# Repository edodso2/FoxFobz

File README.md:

# Fox Fobz

A BLE key fob + receiver that adds keyless lock/unlock to classic cars, starting with the 1988 Fox-body Mustang. A Raytac MDBT50Q (nRF52840) receiver sits in the OEM door-lock circuit and drives the lock motors through DRV8873 H-bridges, so the OEM switches keep working. A Raytac MDBT42T (nRF52805) fob and an iOS app send lock/unlock commands to it.

```
[Fob: MDBT42T]  --BLE broadcast-->  [Receiver: MDBT50Q]  -->  DRV8873 ×2  -->  door lock motors
                                          ^       ^
                         [iOS app] --GATT-+       +-- OEM lock switches (sensed)
```

**Where things stand:** [STATUS.md](STATUS.md) · **Milestones:** [docs/roadmap.md](docs/roadmap.md)

## Repo map

| Folder | What | Version source | Tag prefix |
|---|---|---|---|
| [hardware/receiver/](hardware/receiver/) | Receiver PCB (KiCad 10, 4-layer) | KiCad title block Rev | `receiver-hw/revX` |
| [hardware/fob/](hardware/fob/) | Fob PCB (not started) | KiCad title block Rev | `fob-hw/revX` |
| [hardware/dev-rig/](hardware/dev-rig/) | Breadboard rig for car testing | — | — |
| [firmware/receiver/](firmware/receiver/) | Receiver firmware (NCS 2.7 / Zephyr) | `VERSION` | `receiver-fw/vX.Y.Z` |
| [firmware/fob/](firmware/fob/) | Fob firmware | `VERSION` | `fob-fw/vX.Y.Z` |
| [firmware/common/](firmware/common/) | Shared protocol header | `FOB_PROTO_VERSION` | `protocol/vN` |
| [app/](app/) | iOS app (Flutter) | `pubspec.yaml` version | `app/vX.Y.Z` |
| [web/](web/) | foxfobz.com (Astro + Cloudflare Workers + Stripe) | `package.json` version | `web/vX.Y.Z` |
| [testing/](testing/) | Bench tests, per-vehicle field-test logs, templates | — | — |
| [docs/](docs/) | Roadmap, security, protocol, decisions, backlog, production, datasheets | — | — |
| [business/](business/) | Project brief (shareable overview), business plan, LLC setup, operations | — | — |

## Versioning

Every component evolves and is versioned on its own, in this one repo:

- **Tags are prefixed per component** and annotated (`git tag -a fob-fw/v0.2.0 -m "…"`). List one component's history with `git tag -l 'fob-fw/*'`, or `git log receiver-fw/v0.1.0..receiver-fw/v0.2.0 -- firmware/receiver`.
- **Hardware** gets a letter revision only when boards are ordered. The exact fab files are committed in `hardware/<board>/releases/revX/` ([process](hardware/README.md#revisions-and-releases)).
- **Firmware** uses semver (0.x until field testing passes). Tag when a build goes on a car or ships. Each board prints its version and `git describe` build id at boot.
- **Protocol** changes that break on-air compatibility bump `FOB_PROTO_VERSION` and get a `protocol/vN` tag.
- **[docs/compatibility.md](docs/compatibility.md)** records which hw rev × fw × app combinations were tested together. That's the record for sign-off.

## Quick start

```bash
firmware/scripts/build.sh receiver && firmware/scripts/flash.sh receiver
firmware/scripts/build.sh fob && firmware/scripts/flash.sh fob
cd app && flutter run
cd web && npm ci && npm run dev
```

Open `FoxFobz.code-workspace` in VS Code for per-folder tooling (nRF Connect, Flutter, Astro).

## History

This repo was created on 2026-10-23 as a fresh copy consolidating these archived repos and folders: `~/Documents/FoxFobz` (planning), `~/Development/foxfobz-dev/*` (firmware, app, website, business), and `~/Documents/ki-cad/FoxFobz_Reciever` (`4-layer-experiment` @ `4ef8637`). See their git history for anything earlier.

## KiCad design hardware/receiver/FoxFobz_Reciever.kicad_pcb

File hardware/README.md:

# Hardware

KiCad **10.0** projects, one folder per board.

| Board | Folder | Current rev | Status |
|---|---|---|---|
| Receiver (MDBT50Q-1MV2, 2× DRV8873H, 12 V harness) | [receiver/](receiver/) | revA (unreleased) | Designed, DRC/ERC clean, fab outputs generated. Order pending car test (M2) |
| Fob (MDBT42TV-PAT, CR2032, 2 buttons) | [fob/](fob/) | — | Not started (M3) |
| Dev rig (breadboard + breakouts) | [dev-rig/](dev-rig/) | — | In use for car testing (M1) |

## Revisions and releases

A board **revision** (A, B, C…) is a set of boards that was actually ordered. Edits between orders are just commits.

When placing a JLC order:
1. Set the schematic and PCB title block **Rev** to the letter, and put `revX` on the silkscreen.
2. Run ERC/DRC (`kicad-cli`) and regenerate fab outputs (see [receiver/CLAUDE.md](receiver/CLAUDE.md#fab-outputs-jlcpcb)).
3. Copy exactly what you upload into `<board>/releases/revX/`: gerbers zip, BOM, CPL, a schematic PDF, and the JLC order settings used. This folder is committed. `fab_outputs/` (scratch) stays ignored.
4. Commit, then tag: `git tag -a receiver-hw/revA -m "Receiver revA — JLC order #…"`.
5. Update [STATUS.md](../STATUS.md) and [docs/compatibility.md](../docs/compatibility.md).

Board bring-up and test results go in `testing/`. Problems found on a revision go in that board's `TODO.MD` as next-rev candidates.

## Libraries

Each project keeps its own part libraries (`*.pretty` folders with symbol + footprint + 3D model), referenced through `${KIPRJMOD}` so the folder can move. If the fob reuses receiver parts, move them to `hardware/lib/` and point both projects' lib tables at `${KIPRJMOD}/../lib/...`.

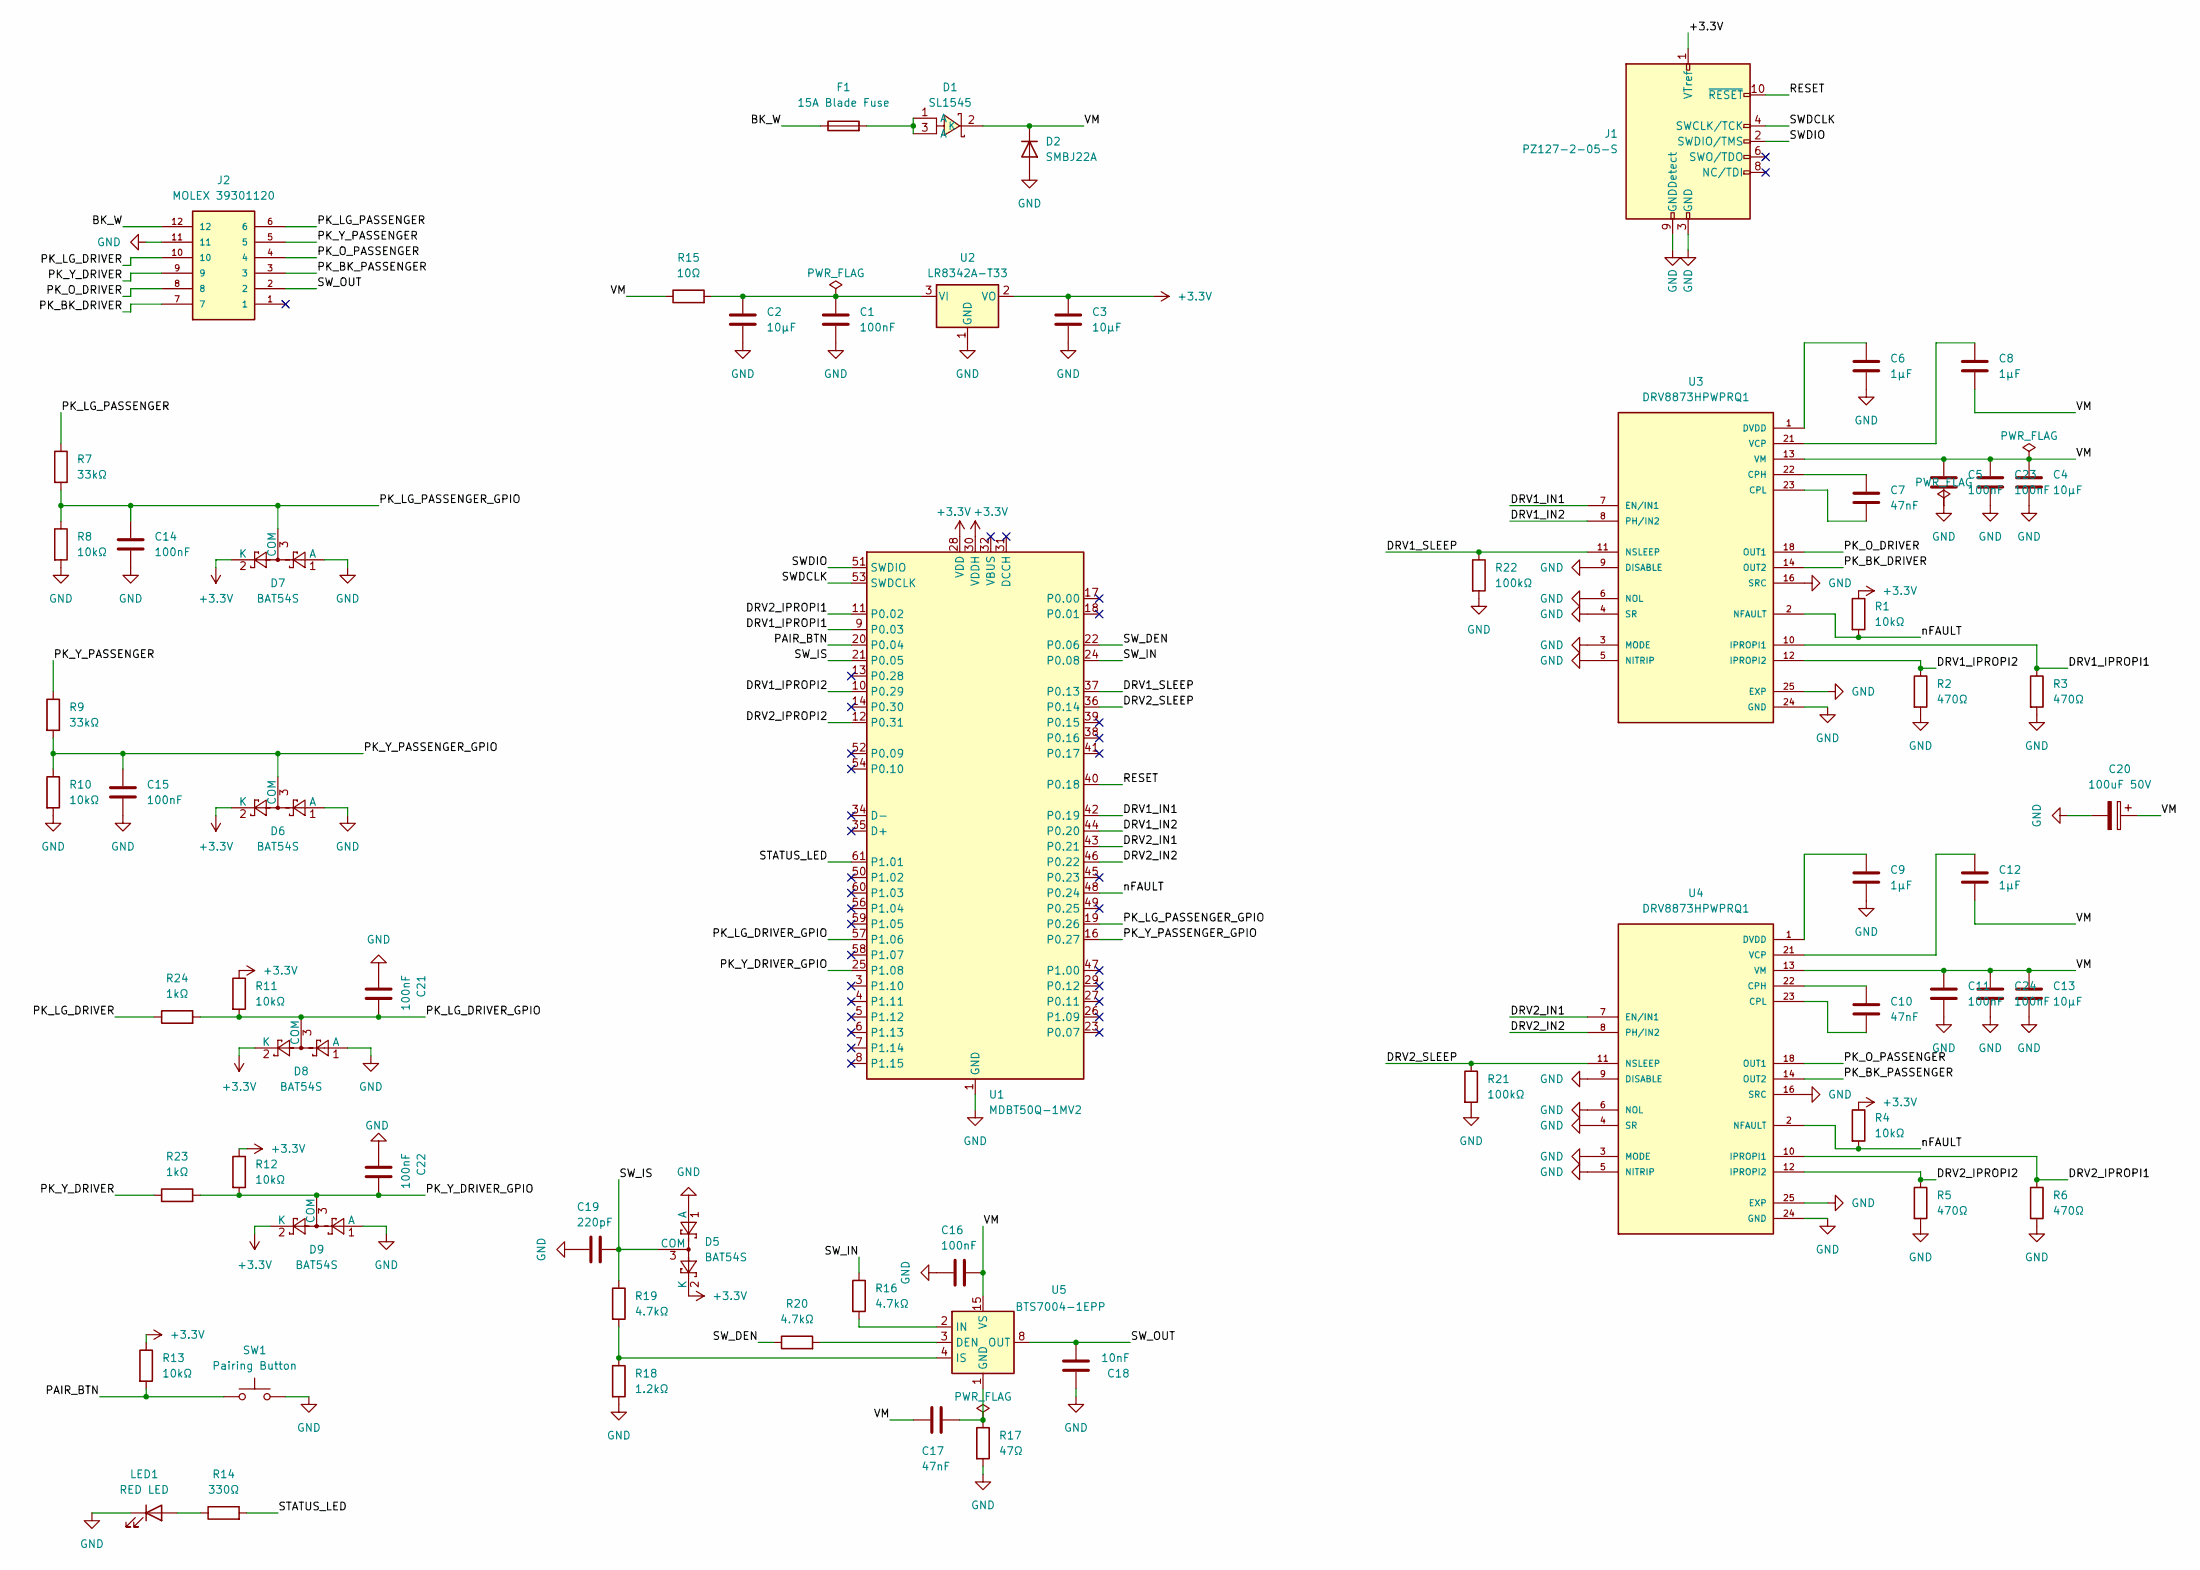
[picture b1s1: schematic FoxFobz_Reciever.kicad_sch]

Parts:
C1, C5, C11, C16, C21, C22, C23, C24: 100nF; C_0402_1005Metric; LCSC C307331
C2, C4, C13: 10µF; C_1206_3216Metric; LCSC C13585
C3: 10µF; C_0805_2012Metric; LCSC C32635
C6, C8, C9, C12: 1µF; C_0402_1005Metric; LCSC C52923
C7, C10, C17: 47nF; C_0402_1005Metric; LCSC C272875
C14, C15: 100nF; C_0402_1005Metric; LCSC C100072
C18: 10nF; C_0402_1005Metric; LCSC C1710
C19: 220pF; C_0402_1005Metric; LCSC C1603
C20: 100uF 50V; CP_Elec_8x10; LCSC C5250964
D1: SL1545; MPN SL1545; LCSC C65022
D2: SMBJ22A; D_SMB; LCSC C726829
D5, D6, D7, D8, D9: BAT54S; SOT-23; LCSC C8592
F1: 15A Blade Fuse; FUSE_3568; LCSC C5249699
J1: PZ127-2-05-S; PinHeader_2x05_P1.27mm_Vertical_SMD; LCSC C3975188
J2: MOLEX 39301120; 39301120; PARTREV F1; LCSC C485574
LED1: RED LED; LED_0805_2012Metric; LCSC C84256
R1, R4, R8, R10, R11, R12, R13: 10kΩ; R_0402_1005Metric; LCSC C25744
R2, R3, R5, R6: 470Ω; R_0402_1005Metric; LCSC C25117
R7, R9: 33kΩ; R_0402_1005Metric; LCSC C25779
R14: 330Ω; R_0402_1005Metric; LCSC C17630
R15: 10Ω; R_0402_1005Metric; LCSC C25077
R16, R19, R20: 4.7kΩ; R_0402_1005Metric; LCSC C174177
R17: 47Ω; R_0402_1005Metric; LCSC C174246
R18: 1.2kΩ; R_0402_1005Metric; LCSC C25862
R21, R22: 100kΩ; R_0402_1005Metric; LCSC C25530
R23, R24: 1kΩ; R_0402_1005Metric; LCSC C11702
SW1: Pairing Button; SW_SPST_TL3342; LCSC C318884
U1: MDBT50Q-1MV2; Raytac_MDBT50Q; LCSC C5118826
U2: LR8342A-T33; SOT-23; LCSC C29781219
U3, U4: DRV8873HPWPRQ1; SOP65P640X120-25N; PARTREV AUG2018; DigiKey_Part_Number 296-50274-1-ND
U5: BTS7004-1EPP; Infineon_PG-TSDSO-14-22; LCSC C3232437

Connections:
+3.3V: C3.1, D5.2 (K), D6.2 (K), D7.2 (K), D8.2 (K), D9.2 (K), J1.1 (VTref), R1.1, R4.1, R11.1, R12.1, R13.1, U1.28 (VDD), U1.30 (VDDH), U2.2 (VO)
/BK_W: F1.1, J2.12
/DRV1_IN1: U1.42 (P0.19), U3.7 (EN/IN1)
/DRV1_IN2: U1.44 (P0.20), U3.8 (PH/IN2)
/DRV1_IPROPI1: R3.1, U1.9 (P0.03), U3.10 (IPROPI1)
/DRV1_IPROPI2: R2.1, U1.10 (P0.29), U3.12 (IPROPI2)
/DRV1_SLEEP: R22.1, U1.37 (P0.13), U3.11 (NSLEEP)
/DRV2_IN1: U1.43 (P0.21), U4.7 (EN/IN1)
/DRV2_IN2: U1.46 (P0.22), U4.8 (PH/IN2)
/DRV2_IPROPI1: R6.1, U1.11 (P0.02), U4.10 (IPROPI1)
/DRV2_IPROPI2: R5.1, U1.12 (P0.31), U4.12 (IPROPI2)
/DRV2_SLEEP: R21.1, U1.36 (P0.14), U4.11 (NSLEEP)
/PAIR_BTN: R13.2, SW1.1, U1.20 (P0.04)
/PK_BK_DRIVER: J2.7, U3.14 (OUT2), U3.15 (OUT2)
/PK_BK_PASSENGER: J2.3, U4.14 (OUT2), U4.15 (OUT2)
/PK_LG_DRIVER: J2.10, R24.1
/PK_LG_DRIVER_GPIO: C21.1, D8.3 (COM), R11.2, R24.2, U1.57 (P1.06)
/PK_LG_PASSENGER: J2.6, R7.1
/PK_LG_PASSENGER_GPIO: C14.1, D7.3 (COM), R7.2, R8.1, U1.19 (P0.26)
/PK_O_DRIVER: J2.8, U3.18 (OUT1), U3.19 (OUT1)
/PK_O_PASSENGER: J2.4, U4.18 (OUT1), U4.19 (OUT1)
/PK_Y_DRIVER: J2.9, R23.1
/PK_Y_DRIVER_GPIO: C22.1, D9.3 (COM), R12.2, R23.2, U1.25 (P1.08)
/PK_Y_PASSENGER: J2.5, R9.1
/PK_Y_PASSENGER_GPIO: C15.1, D6.3 (COM), R9.2, R10.1, U1.16 (P0.27)
/RESET: J1.10 (~RESET), U1.40 (P0.18)
/STATUS_LED: R14.2, U1.61 (P1.01)
/SWDCLK: J1.4 (SWCLK/TCK), U1.53 (SWDCLK)
/SWDIO: J1.2 (SWDIO/TMS), U1.51 (SWDIO)
/SW_DEN: R20.1, U1.22 (P0.06)
/SW_IN: R16.1, U1.24 (P0.08)
/SW_IS: C19.1, D5.3 (COM), R19.1, U1.21 (P0.05)
/SW_OUT: C18.1, J2.2, U5.8 (OUT), U5.9 (OUT), U5.10 (OUT), U5.12 (OUT), U5.13 (OUT), U5.14 (OUT)
/nFAULT: R1.2, R4.2, U1.48 (P0.24), U3.2 (NFAULT), U4.2 (NFAULT)
GND: C1.2, C2.2, C3.2, C4.2, C5.2, C6.2, C9.2, C11.2, C13.2, C14.2, C15.2, C16.2, C18.2, C19.2, C20.2, C21.2, C22.2, C23.2, C24.2, D2.2 (A), D5.1 (A), D6.1 (A), D7.1 (A), D8.1 (A), D9.1 (A), J1.3 (GND), J1.5 (GND), J1.9 (GNDDetect), J2.11, LED1.1 (K), R2.2, R3.2, R5.2, R6.2, R8.2, R10.2, R17.2, R18.2, R21.2, R22.2, SW1.2, U1.1 (GND), U1.2 (GND), U1.15 (GND), U1.33 (GND), U1.55 (GND), U2.1 (GND), U3.3 (MODE), U3.4 (SR), U3.5 (NITRIP), U3.6 (NOL), U3.9 (DISABLE), U3.16 (SRC), U3.17 (SRC), U3.24 (GND), U3.25 (EXP), U3.P1 (EXP), U3.P2 (EXP), U3.P3 (EXP), U3.P4 (EXP), U3.P5 (EXP), U3.P6 (EXP), U3.P7 (EXP), U3.P8 (EXP), U3.P9 (EXP), U3.P10 (EXP), U3.P11 (EXP), U3.P12 (EXP), U3.P13 (EXP), U3.P14 (EXP), U3.P15 (EXP), U3.P16 (EXP), U3.P17 (EXP), U3.P18 (EXP), U4.3 (MODE), U4.4 (SR), U4.5 (NITRIP), U4.6 (NOL), U4.9 (DISABLE), U4.16 (SRC), U4.17 (SRC), U4.24 (GND), U4.25 (EXP), U4.P1 (EXP), U4.P2 (EXP), U4.P3 (EXP), U4.P4 (EXP), U4.P5 (EXP), U4.P6 (EXP), U4.P7 (EXP), U4.P8 (EXP), U4.P9 (EXP), U4.P10 (EXP), U4.P11 (EXP), U4.P12 (EXP), U4.P13 (EXP), U4.P14 (EXP), U4.P15 (EXP), U4.P16 (EXP), U4.P17 (EXP), U4.P18 (EXP)
unnamed: D1.1 (A), D1.3 (A), F1.2
unnamed: LED1.2 (A), R14.1
unnamed: C1.1, C2.1, R15.2, U2.3 (VI)
unnamed: C7.1, U3.22 (CPH)
unnamed: C7.2, U3.23 (CPL)
unnamed: C6.1, U3.1 (DVDD)
unnamed: C8.1, U3.21 (VCP)
unnamed: C10.1, U4.22 (CPH)
unnamed: C10.2, U4.23 (CPL)
unnamed: C9.1, U4.1 (DVDD)
unnamed: C12.1, U4.21 (VCP)
unnamed: R20.2, U5.3 (DEN)
unnamed: C17.1, R17.1, U5.1 (GND)
unnamed: R16.2, U5.2 (IN)
unnamed: R18.1, R19.2, U5.4 (IS)
VM: C4.1, C5.1, C8.2, C11.1, C12.2, C13.1, C16.1, C17.2, C20.1, C23.1, C24.1, D1.2 (K), D2.1 (K), R15.1, U3.13 (VM), U3.20 (VM), U4.13 (VM), U4.20 (VM), U5.15 (VS)

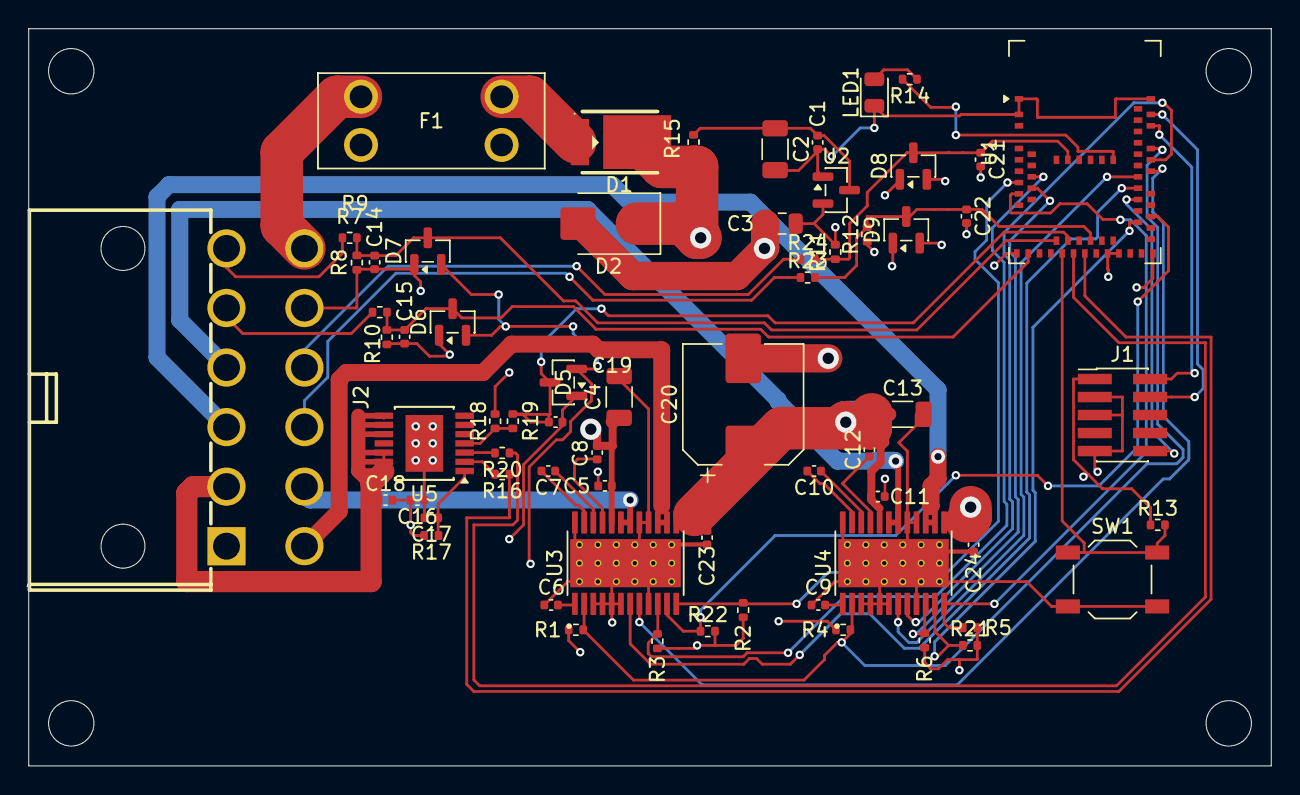
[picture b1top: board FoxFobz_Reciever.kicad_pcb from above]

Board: 4 copper layers, 87.7 x 52.0 mm, 69 parts (0 on the bottom side), 51 nets.

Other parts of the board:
H1, H2, H3, H4: M3; MountingHole_3.2mm_M3
